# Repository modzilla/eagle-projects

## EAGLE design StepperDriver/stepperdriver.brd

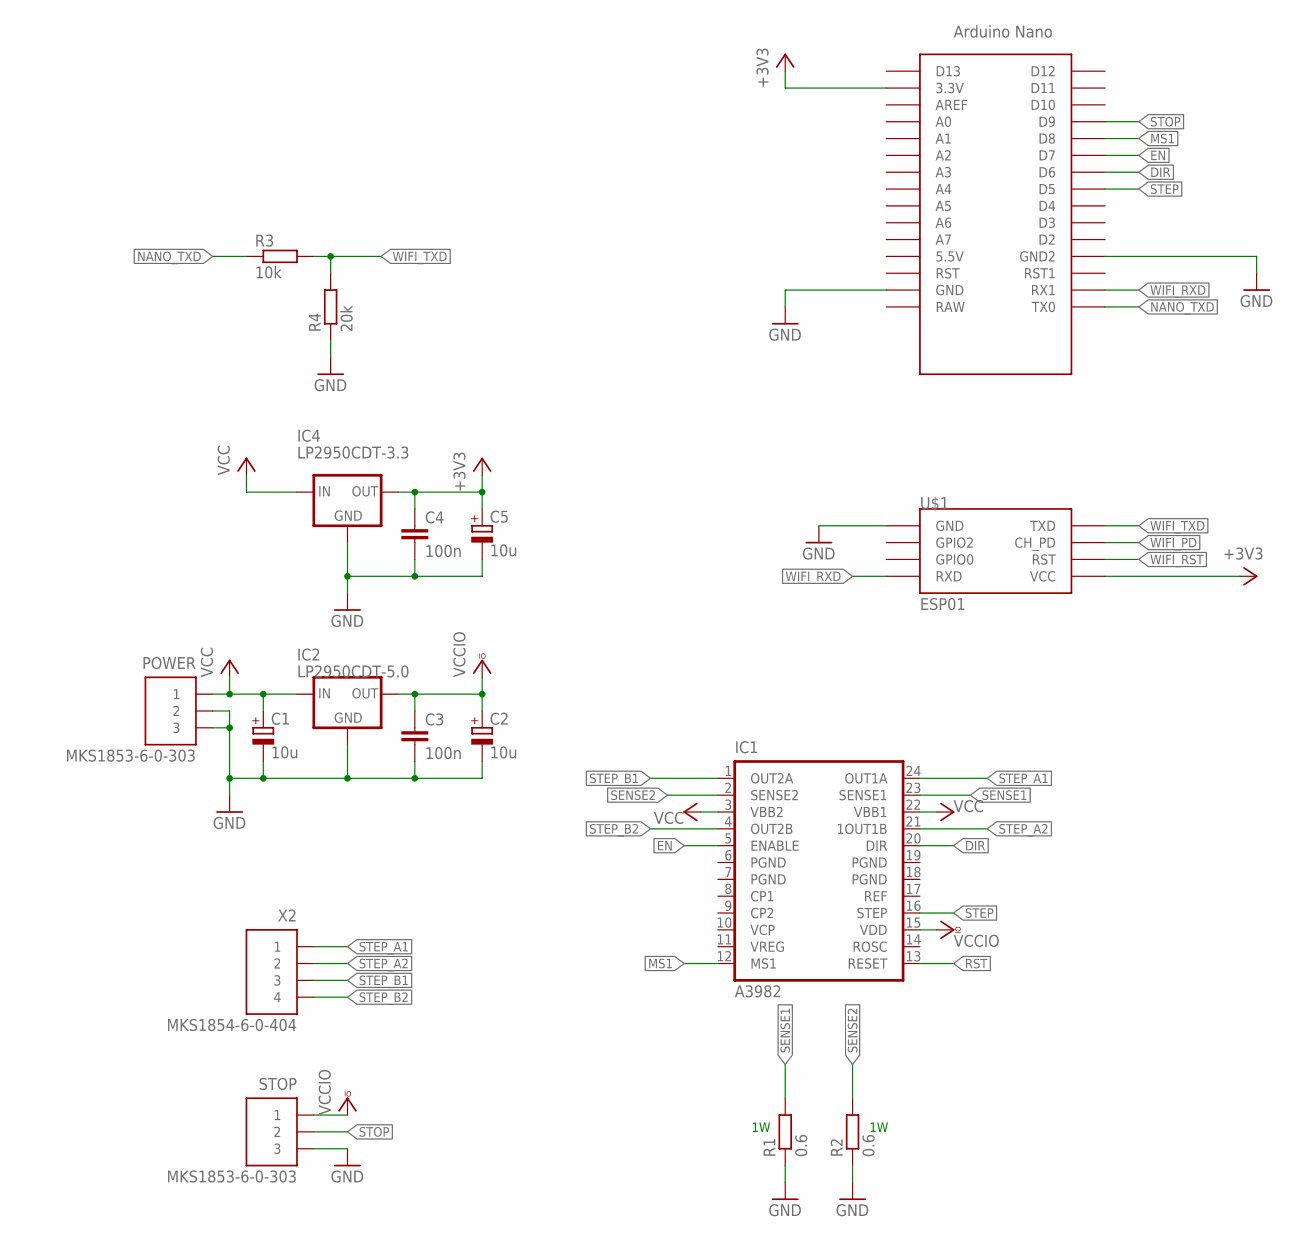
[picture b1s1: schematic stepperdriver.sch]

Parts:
C1, C2, C5: 10u; 085CS_1AR
C3, C4: 100n; C1206
IC1: A3982; SO24W
IC2: LP2950CDT-5.0; DPACK
IC4: LP2950CDT-3.3; DPACK
POWER: MKS1853-6-0-303
R1, R2: 0.6; PRL1632
R3: 10k; R0805
R4: 20k; R0805
STOP: MKS1853-6-0-303
U$1: ESP01
U$2: NANO
X2: MKS1854-6-0-404

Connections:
+3V3: C4.1, C5.+, IC4.3 (OUT), U$1.VCC, U$2.3.3V
DIR: IC1.20 (DIR), U$2.D6
EN: IC1.5 (ENABLE), U$2.D7
GND: C1.-, C2.-, C3.2, C4.2, C5.-, IC2.4 (GND), IC4.4 (GND), POWER.2, POWER.3, R1.1, R2.1, R4.1, STOP.3, U$1.GND, U$2.GND, U$2.GND1 (GND2)
MS1: IC1.12 (MS1), U$2.D8
NANO_TXD: R3.1, U$2.TX0
PGND: IC1.6 (PGND), IC1.7 (PGND), IC1.18 (PGND), IC1.19 (PGND)
RST: IC1.13 (RESET)
SENSE1: IC1.23 (SENSE1), R1.2
SENSE2: IC1.2 (SENSE2), R2.2
STEP: IC1.16 (STEP), U$2.D5
STEP_A1: IC1.24 (OUT1A), X2.1
STEP_A2: IC1.21 (1OUT1B), X2.2
STEP_B1: IC1.1 (OUT2A), X2.3
STEP_B2: IC1.4 (OUT2B), X2.4
STOP: STOP.2, U$2.D9
VCC: C1.+, IC1.3 (VBB2), IC1.22 (VBB1), IC2.1 (IN), IC4.1 (IN), POWER.1
VCCIO: C2.+, C3.1, IC1.15 (VDD), IC2.3 (OUT), STOP.1
WIFI_PD: U$1.CH_PD
WIFI_RST: U$1.RST
WIFI_RXD: U$1.RX (RXD), U$2.RX1
WIFI_TXD: R3.2, R4.2, U$1.TX (TXD)

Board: 2 copper layers, 17 parts (0 on the bottom side), 19 nets, no tracks yet.
